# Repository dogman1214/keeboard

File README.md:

# keeboard

## Overview

This is an ANSI104 layout keyboard. Meaning 100% size, full numpad, and everything. It has creamy gateron milky yellow pro v2 switches, and an esp32 controlling it all. Finally, it is a gasket mount to dampen vibrations, and a silicon pour for the same effect, and to add more weight.  

I created this keyboard because I wasn't really satisfied with the keyboards on the market, and the current keyboard I have now. I want to follow the aesthetic I want, and not some drab boring tech-grey color or whatever, while keeping my own physical case style as well. 

One unique thing i'm proud of is crafting my own Gasket mount system. Instead of using clunky o-ring systems, I designed a brand new board-wide poron tape design. Like foam, it works like a sandwitch above and below the keyboard plate, and designed to provide maximum creamieness.

Editable CAD file: https://drive.google.com/file/d/1waTcEkKPX5QRJGWGog04dOq1EIFDCUFI/view?usp=sharing
Uploading to drive due to the file been 500mb, too large to upload to github.

## Gallery:

---

## ASSEMBLY
1. Solder on the diodes and kailh hotswap sockets
2. Solder in the esp32
3. Plug in the switches, with the plate in the middle
4. place PORON foam in the gasket mounts sandwitch style
5. place the plate in between the gaskets
6. place heatset inserts in bottom and screw in m3 screws via the top
7. flash firmware
8. Pour in the silicon pour underneath the PCB, make sure to seal it off with seran wrap first.
9. enjoy!

# Bill of Materials (BOM)

### Electronics & Hardware

| Item | Description | Cost (Pre‑Tax) | Link |
| :--- | :--- | :--- | :--- |
| Switches | Gateron Milky Yellow Pro V2 | $25.90 | https://www.amazon.com/gp/product/B0C2CZJQHT |
| Rotary Encoder | ALPS EC11 THT 20k thread-blue vertical switch (H: 20mm) | $5.58 | https://mouser.com |
| Keycaps | PBT green, MOA profile | $24.99 | https://www.amazon.com/gp/product/B0F914Q43R |
| Diodes | 1N4148 SMD (Qty: 104), SOD‑123 | $0.18/unit | https://www.mouser.com/en/ProductDetail/Diodes-Incorporated/1N4148W-7-F |
| Stabilizers | Durock V3 screw‑in | $25.99 | https://www.amazon.com/dp/B0B2RW12S2 |
| PCB | Custom PCB | $45 | AIVON (with $30 discount applied) |
| Kailh Hotswap Sockets | 120 pcs | $13.20 | https://mechanicalkeyboards.com/products/kailh-switch-hot-swap-socket |
| ESP32‑S3 DevKitC‑1 (N16R8) | MCU | $8.99 | https://www.amazon.com/dp/B0GBT212KM |
| Cyanoacrylate Glue | CA super glue | $5.99 | https://www.amazon.com/dp/B0DYJPW9GK |

### Fasteners & Case Hardware

| Item | Description | Cost | Link |
| :--- | :--- | :--- | :--- |
| M3 Heatset Inserts | Brass | $6.99 | https://www.amazon.com/dp/B0FWWW8VP1 |
| M3 Screws | Assorted set | $6.99 | https://www.amazon.com/dp/B0D3X5CT2J |
| 3D Printed Case | Custom | — | — |
| 3D Printed Plate | Custom | — | — |
| 3D Printed Knob | EC11 compatible | — | — |
| Adhesive Transfer Tape | 3M Scotch 924 ATG | $9.57 | https://www.amazon.com/dp/B00FFDUG9M |

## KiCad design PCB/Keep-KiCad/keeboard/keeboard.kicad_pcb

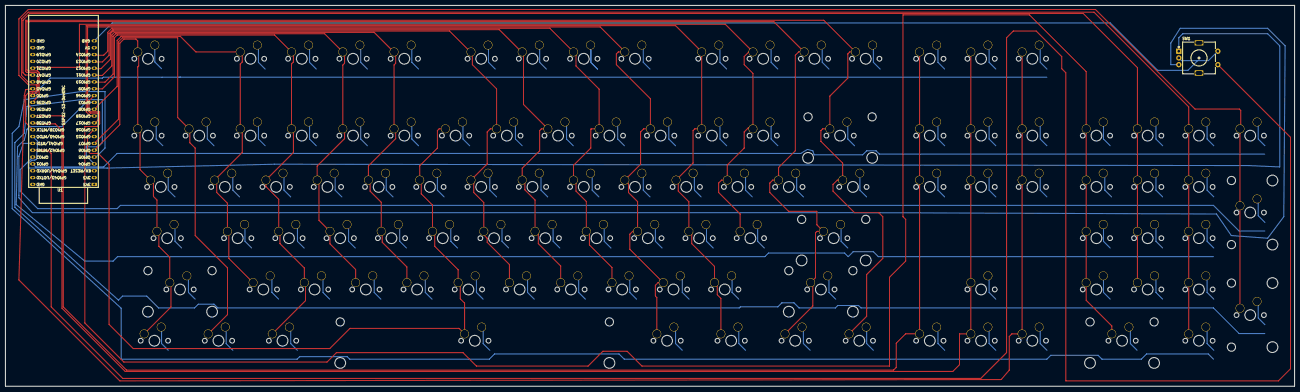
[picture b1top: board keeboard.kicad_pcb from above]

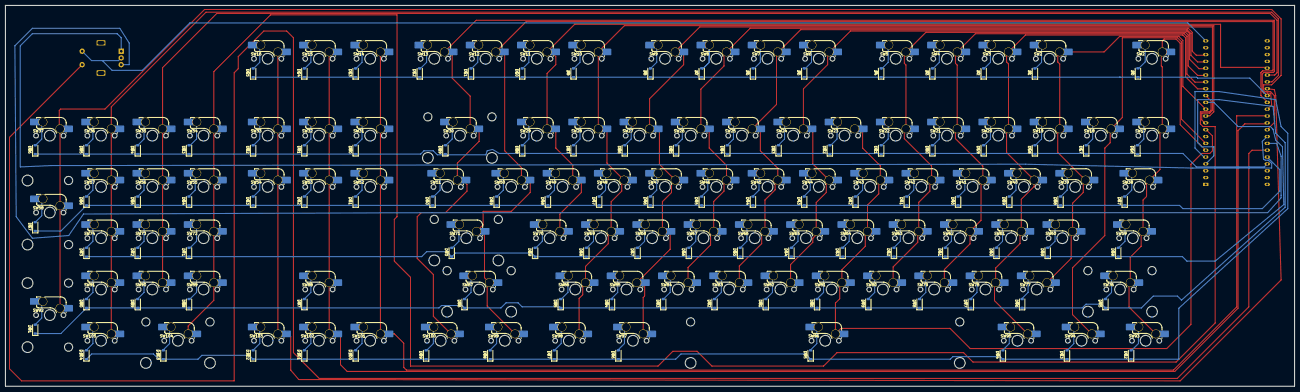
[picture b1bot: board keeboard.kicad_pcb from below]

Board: 2 copper layers, 479.0 x 141.5 mm, 218 parts (208 on the bottom side), 25 nets.

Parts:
D0, D1, D2, D3, D4, D5, D6, D7, D8, D9, D10, D11, D12, D13, D14, D15, D16, D17, D18, D19, D20, D21, D22, D23, D24, D25, D26, D27, D28, D29, D30, D31, D32, D33, D34, D35, D36, D37, D38, D39, D40, D41, D42, D43, D44, D45, D46, D47, D48, D49, D50, D51, D52, D53, D54, D55, D56, D57, D58, D59, D60, D61, D62, D63, D64, D65, D66, D67, D68, D69, D70, D71, D72, D73, D75, D76, D77, D78, D79, D80, D81, D82, D83, D84, D85, D86, D87, D88, D89, D90, D91, D92, D93, D94, D95, D96, D97, D98, D99, D100, D101, D102, D103, D104: 1N4148; D_SOD-123
S1, S2, S3, S4: MX_stab; STAB_MX_2u
S5, S8: MX_stab; STAB_MX_2.25u
S6: MX_stab; STAB_MX_2.75u
S7: MX_stab; STAB_MX_6.25u
SW1: RotaryEncoder_Switch; RotaryEncoder_Alps_EC11E-Switch_Vertical_H20mm
SW2, SW2#2, SW3, SW4, SW5, SW6, SW7, SW8, SW9, SW10, SW11, SW12, SW13, SW14, SW15, SW16, SW17, SW18, SW19, SW20, SW21, SW22, SW23, SW24, SW25, SW26, SW27, SW28, SW29, SW30, SW31, SW32, SW33, SW34, SW35, SW36, SW37, SW38, SW39, SW40, SW41, SW42, SW43, SW44, SW45, SW46, SW47, SW48, SW49, SW50, SW51, SW52, SW53, SW54, SW55, SW56, SW57, SW58, SW59, SW60, SW61, SW62, SW63, SW64, SW65, SW66, SW67, SW68, SW69, SW70, SW71, SW72, SW73, SW74, SW76, SW77, SW78, SW79, SW80, SW81, SW82, SW83, SW84, SW85, SW86, SW87, SW88, SW89, SW90, SW91, SW92, SW95, SW96, SW97, SW98, SW99, SW100, SW101, SW102, SW105: SW_Push; SW_MX_HS_CPG151101S11_1u
SW93, SW94, SW103, SW104: SW_Push; SW_MX_HS_CPG151101S11_1.25u
U1: ESP32-S3-DevKitC

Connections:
/COL0: SW2.1, SW60.1, SW93.1, U1.6 (GPIO6/ADC1_CH5)
/COL1: SW19.1, SW40.1, SW61.1, SW76.1, SW94.1, U1.7 (GPIO7/ADC1_CH6)
/COL2: SW3.1, SW20.1, SW41.1, SW62.1, SW77.1, SW95.1, U1.12 (GPIO8/ADC1_CH7)
/COL3: SW4.1, SW21.1, SW42.1, SW63.1, SW78.1, U1.15 (GPIO9/ADC1_CH8)
/COL4: SW5.1, SW22.1, SW43.1, SW64.1, SW79.1, U1.16 (GPIO10/ADC1_CH9)
/COL5: SW6.1, SW23.1, SW44.1, SW65.1, SW80.1, SW96.1, U1.17 (GPIO11/ADC2_CH0)
/COL6: SW7.1, SW24.1, SW45.1, SW66.1, SW81.1, U1.18 (GPIO12/ADC2_CH1)
/COL7: SW8.1, SW25.1, SW46.1, SW67.1, SW82.1, U1.19 (GPIO13/ADC2_CH2)
/COL8: SW9.1, SW26.1, SW47.1, SW68.1, SW83.1, U1.20 (GPIO14/ADC2_CH3)
/COL9: SW10.1, SW27.1, SW48.1, SW69.1, SW84.1, U1.10 (GPIO17/ADC2_CH6)
/COL10: SW11.1, SW28.1, SW49.1, SW70.1, SW85.1, SW97.1, U1.11 (GPIO18/ADC2_CH7)
/COL11: SW12.1, SW29.1, SW50.1, SW71.1, SW86.1, SW98.1, U1.27 (GPIO21)
/COL12: SW13.1, SW30.1, SW51.1, SW72.1, SW87.1, SW99.1, U1.32 (GPIO35)
/COL13: SW14.1, SW31.1, SW52.1, SW100.1, U1.33 (GPIO36)
/COL14: SW15.1, SW32.1, SW53.1, SW101.1, U1.34 (GPIO37)
/COL15: SW16.1, SW33.1, SW54.1, SW88.1, SW102.1, U1.35 (GPIO38)
/COL16: SW17.1, SW34.1, SW55.1, SW103.1, U1.30 (GPIO45)
/COL17: SW35.1, SW56.1, SW73.1, SW89.1, SW104.1, U1.14 (GPIO46)
/COL18: SW36.1, SW57.1, SW74.1, SW90.1, U1.28 (GPIO47)
/COL19: SW37.1, SW58.1, SW91.1, SW105.1, U1.29 (GPIO48)
/COL20: SW38.1, SW59.1, SW92.1, U1.36 (GPIO39/MTCK)
GND: SW1.C, SW1.S2, U1.22 (GND), U1.23 (GND), U1.24 (GND), U1.44 (GND)
unnamed: SW1.A, U1.37 (GPIO40/MTDO)
unnamed: SW1.B, U1.38 (GPIO41/MTDI)
unnamed: SW1.S1, U1.39 (GPIO42/MTMS)
